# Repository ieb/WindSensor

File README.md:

# Sailing Wind Sensor

This project contains the code and designed for a long arm sailing wind sensor. Standard wind sensors are fine for most sails but they fail to acurately measure wind angle down wind where they are in the flow of the air from the mainsail. This is partically bad where the mainsail has a large flat top. (Class40, Pogo1250, etc). The solution is to put the windsensor on a 1m-1.8m carbon mast above the masthead. Commercially these sensors start at 1K GBP and for 1.8m sensors expect to pay 4K GBP. Hence this project attempts to create a wind sensor using opensource components.

Construction
The housing is 3D printed in ABS. The mast is laminated in carbon fibre. 

Communications
Raymarine uses a 2 axis hall device generating sin/cos voltages and a pulse for speed. The circuit is complex, large and suceptable to errors in the voltages due to the length of wire run and poor connections. For that reason, although I currently have a Raymarine wind sensor I decided not to duplicate.

The device will communicates with RF using a Beken BK2491 chipset configured in the form a a JDY-40 runing at 2Mb/s bursting a serial stream at 9600 baud.

https://www.mikrocontroller.net/attachment/381910/BT-WiFi-52rf5541.pdf
https://www.electrodragon.com/w/images/0/05/EY-40_English_manual.pdf

The data sent over RF has 2 forms running at between 5-10Hz, both comma seperated values with a CRC16 checksum.

The protocol is proprietary and compact. A single line of csv readings without interpretation including the reading from the possition sensor 12bit representing 0-360 and the number of nano seconds for half a revolution (64bit).

* Masthead micro controller - Ardiono Pro Mini (18mmx33mm, 8MHz, 3.3v).
* Angular sensor - AS5600 12bit i2C device sensing a diametrically magnatised magnet
* Speed sensor - SS451 Hall switch sensing 2 magnets on a shaft triggering interrupts.
* JDY-40 - 2.4GHz RF module running at 9600 baud bursting over a 2Mb/s wifi channel.
* Supply 11-16V

Measurements.

The measurements including writing to the serial take 4ms to complete. Resolution of the AS5600 is 0.1 degrees. The code measures the pulse period directly since at low speed counting pulses is inacurage. Slowest speed is 1 revolution every 64s which is 0.01Kn. Highest is probably limimited mechanically but is well over 100kn (tested with a drill driving the shaft)

Calibration Curve for AS5600, depends completly on the hardware setup.

        0,709,69,2070
        10,822,69,2078
        20,939,69,2083
        30,1049,69,2086
        40,1167,69,2090
        50,1283,69,2092
        60,1396,69,2098
        70,1512,69,2104
        80,1625,69,2110
        90,1736,69,2117
        100,1853,69,2117
        110,1964,69,2113
        120,2082,69,2112
        130,2196,69,2126
        140,2308,69,2122
        150,2423,69,2117
        160,2536,69,2120
        170,2649,69,2122
        180,2762,69,2119
        190,2874,69,2112
        200,2987,67,2106
        210,3103,67,2096
        220,3216,67,2087
        230,3326,67,2081
        240,3438.67.2086
        250,3549,67,2079
        260,3661,67,2062
        270,3776,67,2057
        280,2883,67,2054
        290,3997,69,2077
        300,14,69,2075
        290,4000,69,2081
        295,4054,69,2078
        298,5092,69,2076
        300,18,69,2078
        310,127,69,2063
        320,244,69,2054
        330,358,69,2053
        340,475,69,2056
        350,590,69,2061
        0,702,69,2070
        64,1439,,
        334,406,,
        253,3586,,
        93,1778,,
        301,57,,
        127,2188,,
        32,1097,,
        287,3982,,

Conversion to degrees is 360*(m-offset)/4096. Average error is 0.3 degrees,
There appears to be a sinusoidal error associated with magnet offset, although this is not large enough to be
of concern or to both fixing. Just as likely to be a measurement error.

Conversion and linearisation will be done in the base station, not in the masthead sensor.

Problems encountered

FLoating dir pin on the AS5600 causes erratic readings.
AGC of 50-70 and Flux magnitude of 2000+ gives very stable readings, magnet is a 6mmx4mm Samarium Cobalt Magnet magnet with 0.3kg pull https://www.magnetexpert.com/magnet-materials-standard-assemblies-c150/6mm-dia-x-4mm-thick-diametrically-magnetised-samarium-cobalt-magnet-0-3kg-pull-p3517

The 3144 needs magnets to pass 1mm or less from the surface using 3mmx1mm N35 Neodymium magnet with 0.13kg pull (using 2x)

https://www.magnetexpert.com/magnet-materials-standard-assemblies-c150/3mm-dia-x-1mm-thick-n35-neodymium-magnet-0-13kg-pull-p6201 

Initial attempts to use RS-485 and RS-422 failed due to current consumption runnng the drivers exceeding the output available from the Pro Mini. Also managed to blow multiple Pro Mini's and 1 AS5600 when testing with long wires. the JDY-40 appears to have at least 50m range though walls and metal roofs with minimal data corruption.

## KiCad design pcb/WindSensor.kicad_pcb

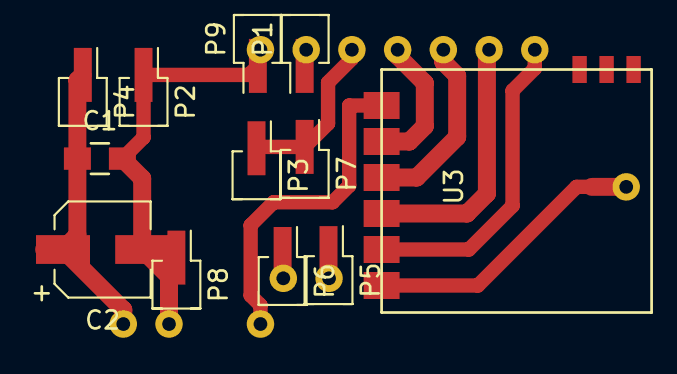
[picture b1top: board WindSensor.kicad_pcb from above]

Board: 2 copper layers, 13 parts (1 on the bottom side), 11 nets.

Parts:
C1: 10nF; C_0805_HandSoldering
C2: 10nF; CP_Elec_5x5.8
P1, P4: SP; Pin_Header_Straight_1x01_Pitch2.54mm_SMD_Pin1Left
P2: 0V; Pin_Header_Straight_1x01_Pitch2.54mm_SMD_Pin1Left
P3: 3v3; Pin_Header_Straight_1x01_Pitch2.54mm_SMD_Pin1Left
P5: SDA; Pin_Header_Straight_1x01_Pitch2.54mm_SMD_Pin1Left
P6: SCL; Pin_Header_Straight_1x01_Pitch2.54mm_SMD_Pin1Left
P7: 5V; Pin_Header_Straight_1x01_Pitch2.54mm_SMD_Pin1Left
P8, P9: GND; Pin_Header_Straight_1x01_Pitch2.54mm_SMD_Pin1Left
U1: ArdinoMinPro; ArduinoProMini
U3: JDY40; JDY-40

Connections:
3v3: U1.21, U3.9
5V: C1.1, C2.1, P4.1, U1.24
DE: U1.9, U3.12
GND: C1.2, C2.2, P2.1, P8.1, P9.1, U1.4, U1.23, U1.31, U3.14
RFEN: U1.10, U3.13
RX: U1.8, U3.11
SCL: P6.1, U1.A5
SDA: P5.1, U1.A4
SENSOR_EN: P3.1, P7.1, U1.6
SPEED: P1.1, U1.5
TX: U1.7, U3.10

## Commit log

2020-12-25 Initial Commit, first working board with RF
2021-01-04 Modularised the libraries and added unit tests, updated pcb, working version
2021-01-18 Using jdy library and fixed memory issues
2021-01-18 Fixing #1, thank you
2021-01-24 Switched to 3v hall device, fixed speed sensor to deal with pulse width variations
2021-03-20 Fixed missing windspeed ouptput
